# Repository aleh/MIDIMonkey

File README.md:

# MIDIMonkey

Listens to MIDI messages on one pin and triggers drums on the other pins (4 or 5 pins for ATtiny85).

I needed this when making analogue drums loosely following [this schematics from Delptronics](http://mickeydelp.com/blog/anatomy-of-a-drum-machine). I did not want to make a hardware sequencer, so opted to making a simple MIDI input instead.

The code is for ATtiny85, but should work on any Arduino. (For ATtiny85 you can use "Digispark (8mhz - no USB)" board in the Arduino IDE.)

## Schematics

This one is for ATtiny85 but should be easy to apply to any Arduino.

---

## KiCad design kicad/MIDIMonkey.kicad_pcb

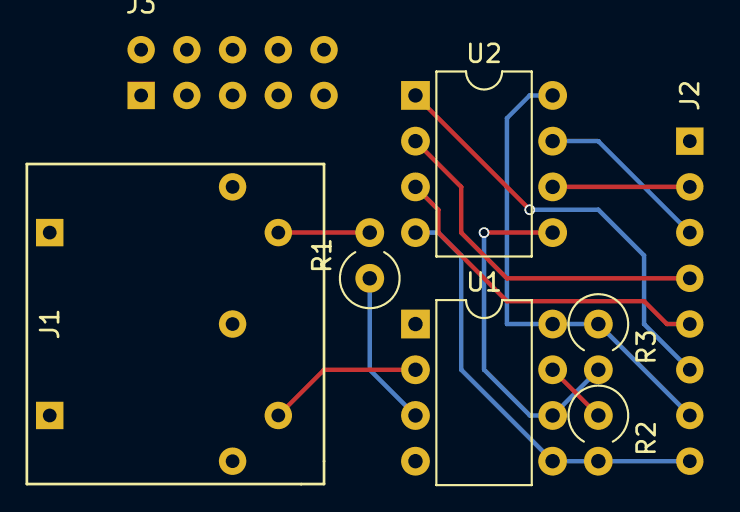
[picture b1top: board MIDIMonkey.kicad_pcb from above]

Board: 2 copper layers, 8 parts (0 on the bottom side), 12 nets.

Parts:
J1: MIDI IN; PROTO_MIDI
J2: OUTPUTS; PROTO_8
J3: ISP; PROTO_2x5
R1: 200; R_Axial_DIN0309_L9.0mm_D3.2mm_P2.54mm_Vertical
R2: 1K; R_Axial_DIN0309_L9.0mm_D3.2mm_P2.54mm_Vertical
R3: 5K1; R_Axial_DIN0309_L9.0mm_D3.2mm_P2.54mm_Vertical
U1: 6N138; DIP-8_W7.62mm
U2: ATtiny85; DIP-8_W7.62mm

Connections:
+5V: J2.7, J3.2, R3.1, U1.8, U2.8
GND: J2.8, J3.10, R2.2, U1.5, U2.4
MISO: J2.2, J3.9, U2.6
MOSI: J3.1, R3.2, U1.6, U2.5
unnamed: J1.4, U1.2
unnamed: J1.5, R1.2
unnamed: R1.1, U1.3
unnamed: R2.1, U1.7
RST: J2.6, J3.5, U2.1
SCK: J2.3, J3.7, U2.7
TRIG3: J2.4, U2.2
TRIG4: J2.5, U2.3

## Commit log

2018-05-01 Got rid of the kicad project file
